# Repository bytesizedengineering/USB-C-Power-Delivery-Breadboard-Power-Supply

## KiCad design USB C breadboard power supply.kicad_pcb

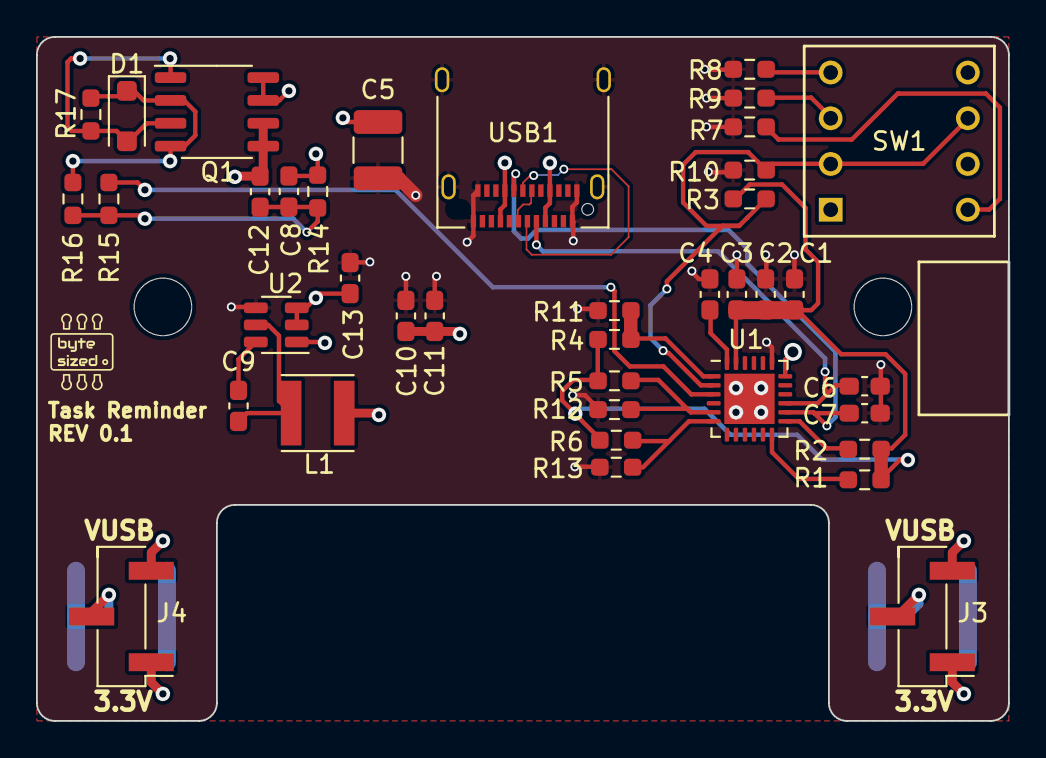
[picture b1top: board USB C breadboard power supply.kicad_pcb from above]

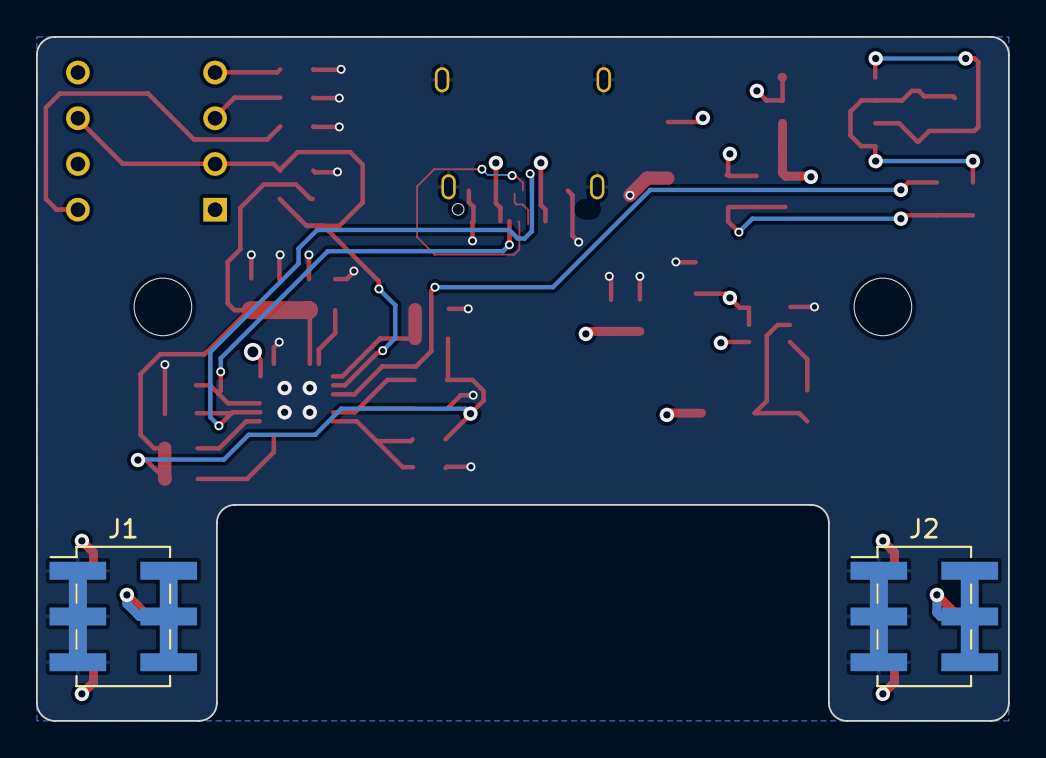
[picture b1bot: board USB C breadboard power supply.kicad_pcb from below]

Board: 4 copper layers, 54.0 x 38.0 mm, 42 parts (2 on the bottom side), 27 nets.

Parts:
C1, C2, C9: 0.1uF; C_0603_1608Metric_Pad1.08x0.95mm_HandSolder
C3, C8, C12: 1uF; C_0603_1608Metric_Pad1.08x0.95mm_HandSolder
C4: C; C_0603_1608Metric_Pad1.08x0.95mm_HandSolder
C5: 3.3uF; C_1210_3225Metric_Pad1.33x2.70mm_HandSolder
C6, C7: 390pF; C_0603_1608Metric_Pad1.08x0.95mm_HandSolder
C10, C11: 22uF; C_0603_1608Metric_Pad1.08x0.95mm_HandSolder
C13: 10uF; C_0603_1608Metric_Pad1.08x0.95mm_HandSolder
D1: D_Zener; D_SOD-123F
H2: MountingHole; MountingHole_3.2mm_M3
J1, J2: Conn_02x02_Counter_Clockwise; PinHeader_2x03_P2.54mm_Vertical_SMD
J3, J4: PinHeader_1x03_P2.54mm_Vertical_SMD_Pin1Left
L1: 4.7uH; L_Vishay_IFSC-1515AH_4x4x1.8mm
Q1: IRF9358TRPBF; SO-8_3.9x4.9mm_P1.27mm
R1, R2: 2K; R_0603_1608Metric_Pad0.98x0.95mm_HandSolder
R3, R5, R6, R7: 5k; R_0603_1608Metric_Pad0.98x0.95mm_HandSolder
R4, R10: DNP; R_0603_1608Metric_Pad0.98x0.95mm_HandSolder
R8: 2.4k; R_0603_1608Metric_Pad0.98x0.95mm_HandSolder
R9, R15: 1k; R_0603_1608Metric_Pad0.98x0.95mm_HandSolder
R11: X; R_0603_1608Metric_Pad0.98x0.95mm_HandSolder
R12, R13, R14: 10k; R_0603_1608Metric_Pad0.98x0.95mm_HandSolder
R16: 0; R_0603_1608Metric_Pad0.98x0.95mm_HandSolder
R17: 49.9k; R_0603_1608Metric_Pad0.98x0.95mm_HandSolder
SW1: SS-10-15SP-LE; SS-10-15SP-LE_NDC
U1: CYPD3177-24LQXQT; QFN-24-1EP_4x4mm_P0.5mm_EP2.8x2.8mm
U2: AP63203WU; TSOT-23-6
USB1: USB_C_Receptacle; USB_C_Receptacle_Amphenol_12401610E4-2A

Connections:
/3V3: C1.1, C2.1, C3.1, R1.1, R2.1, R3.1, R4.1, R5.1, R6.1, U1.23 (VDDD)
/3V3_OUT: C10.1, C11.1, J3.1, J4.1, L1.2, U2.1 (FB)
/CC1: C6.1, U1.15 (CC1), USB1.A5 (CC1)
/CC2: C7.1, U1.14 (CC2), USB1.B5 (CC2)
/D+: USB1.A6 (D+), USB1.B6 (D+)
/D-: USB1.A7 (D-), USB1.B7 (D-)
/DC_OUTPUT: C12.2, J3.3, J4.3, Q1.5, Q1.6
/HPI_SCL: R2.2, U1.13 (HPI_SCL)
/HPI_SDA: R1.2, U1.12 (HPI_SDA)
/ISNK_COARSE: R5.2, R12.1, U1.5 (ISNK_COARSE)
/ISNK_FINE: R6.2, R13.1, U1.6 (ISNK_FINE)
/RAIL_1: J1.2, J1.4, J1.6, J3.2
/RAIL_2: J2.2, J2.4, J2.6, J4.2
/VBUS_FET_EN: R15.2, U1.3 (VBUS_FET_EN)
/VBUS_MAX: R3.2, R10.1, SW1.2 (C), SW1.6 (C), U1.2 (VBUS_MAX)
/VBUS_MIN: R4.2, R11.1, U1.1 (VBUS_MIN)
/VCCD: C4.1, U1.24 (VCCD)
GND: C1.2, C2.2, C3.2, C4.2, C5.2, C6.2, C7.2, C10.2, C11.2, C13.1, J1.1, J1.3, J1.5, J2.1, J2.3, J2.5, R7.1, R8.1, R9.1, R10.2, R11.2, R12.2, R13.2, U1.19 (GND), U1.25 (EPAD), U2.4 (GND), USB1.A1 (GND), USB1.A12 (GND), USB1.B1 (GND), USB1.B12 (GND), USB1.S1 (SHIELD)
unnamed: C8.2, C12.1, R14.2, R15.1, R16.1
unnamed: D1.2 (A), Q1.1, Q1.3, R17.2
unnamed: D1.1 (K), Q1.2, Q1.4, R16.2, R17.1
unnamed: R9.2, SW1.3 (2)
unnamed: R8.2, SW1.4 (3)
unnamed: R7.2, SW1.8 (4)
unnamed: C9.2, U2.6 (BST)
unnamed: C9.1, L1.1, U2.5 (SW)
VBUS: C5.1, C8.1, C13.2, Q1.7, Q1.8, R14.1, U1.18 (VBUS_IN), U2.2 (EN), U2.3 (IN), USB1.A4 (VBUS), USB1.A9 (VBUS), USB1.B4 (VBUS), USB1.B9 (VBUS)

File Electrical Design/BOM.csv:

"Reference","Value","Datasheet","Footprint","Qty","DNP"
"C1,C2,C9","0.1uF","~","Capacitor_SMD:C_0603_1608Metric_Pad1.08x0.95mm_HandSolder","3",""
"C3,C4,C8,C12","1uF","~","Capacitor_SMD:C_0603_1608Metric_Pad1.08x0.95mm_HandSolder","4",""
"C5","3.3uF","~","Capacitor_SMD:C_1210_3225Metric_Pad1.33x2.70mm_HandSolder","1",""
"C6,C7","390pF","~","Capacitor_SMD:C_0603_1608Metric_Pad1.08x0.95mm_HandSolder","2",""
"C10,C11","22uF","~","Capacitor_SMD:C_0603_1608Metric_Pad1.08x0.95mm_HandSolder","2",""
"C13","10uF","~","Capacitor_SMD:C_0603_1608Metric_Pad1.08x0.95mm_HandSolder","1",""
"D1","D_Zener","~","Diode_SMD:D_SOD-123F","1",""
"H1,H2","MountingHole","~","MountingHole:MountingHole_3.2mm_M3","2",""
"J1,J2","Conn_02x02_Counter_Clockwise","~","Connector_PinHeader_2.54mm:PinHeader_2x03_P2.54mm_Vertical_SMD","2",""
"J3,J4","~","~","Connector_PinHeader_2.54mm:PinHeader_1x03_P2.54mm_Vertical_SMD_Pin1Left","2",""
"L1","4.7uH","IFSC1515AHER4R7M01","Inductor_SMD:L_Vishay_IFSC-1515AH_4x4x1.8mm","1",""
"Q1","IRF9358TRPBF","IRF9358TRPBF","Package_SO:SO-8_3.9x4.9mm_P1.27mm","1",""
"R1,R2","2K","~","Resistor_SMD:R_0603_1608Metric_Pad0.98x0.95mm_HandSolder","2",""
"R3,R5,R7","5k","~","Resistor_SMD:R_0603_1608Metric_Pad0.98x0.95mm_HandSolder","3",""
"R4,R6,R10","DNP","~","Resistor_SMD:R_0603_1608Metric_Pad0.98x0.95mm_HandSolder","3",""
"R8,R12","2.4k","~","Resistor_SMD:R_0603_1608Metric_Pad0.98x0.95mm_HandSolder","2",""
"R9,R15","1k","~","Resistor_SMD:R_0603_1608Metric_Pad0.98x0.95mm_HandSolder","2",""
"R11,R13","X","~","Resistor_SMD:R_0603_1608Metric_Pad0.98x0.95mm_HandSolder","2",""
"R14","10k","~","Resistor_SMD:R_0603_1608Metric_Pad0.98x0.95mm_HandSolder","1",""
"R16","0","~","Resistor_SMD:R_0603_1608Metric_Pad0.98x0.95mm_HandSolder","1",""
"R17","49.9k","~","Resistor_SMD:R_0603_1608Metric_Pad0.98x0.95mm_HandSolder","1",""
"SW1","SS-10-15SP-LE","SS-10-15SP-LE","Project footprints:SS-10-15SP-LE_NDC","1",""
"U1","CYPD3177-24LQXQT","CYPD3177-24LQXQT","Package_DFN_QFN:QFN-24-1EP_4x4mm_P0.5mm_EP2.8x2.8mm","1",""
"U2","AP63203WU","https://www.diodes.com/assets/Datasheets/AP63200-AP63201-AP6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","Package_TO_SOT_SMD:TSOT-23-6","1",""
"USB1","USB_C_Receptacle","https://www.usb.org/sites/default/files/documents/usb_type-c.zip","Connector_USB:USB_C_Receptacle_Amphenol_12401610E4-2A","1",""

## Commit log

2024-03-03 Update C4 value
2024-03-05 Updated PCB layout
    Reset the layout grid to use 1mm spacing. Changed board outline size. Adjusted copper fill zones and moved them to different layers. Added logo and moved some silkscreen objects.
2024-06-19 updated design
